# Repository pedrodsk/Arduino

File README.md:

# Arduino

## Some projects with arduino.

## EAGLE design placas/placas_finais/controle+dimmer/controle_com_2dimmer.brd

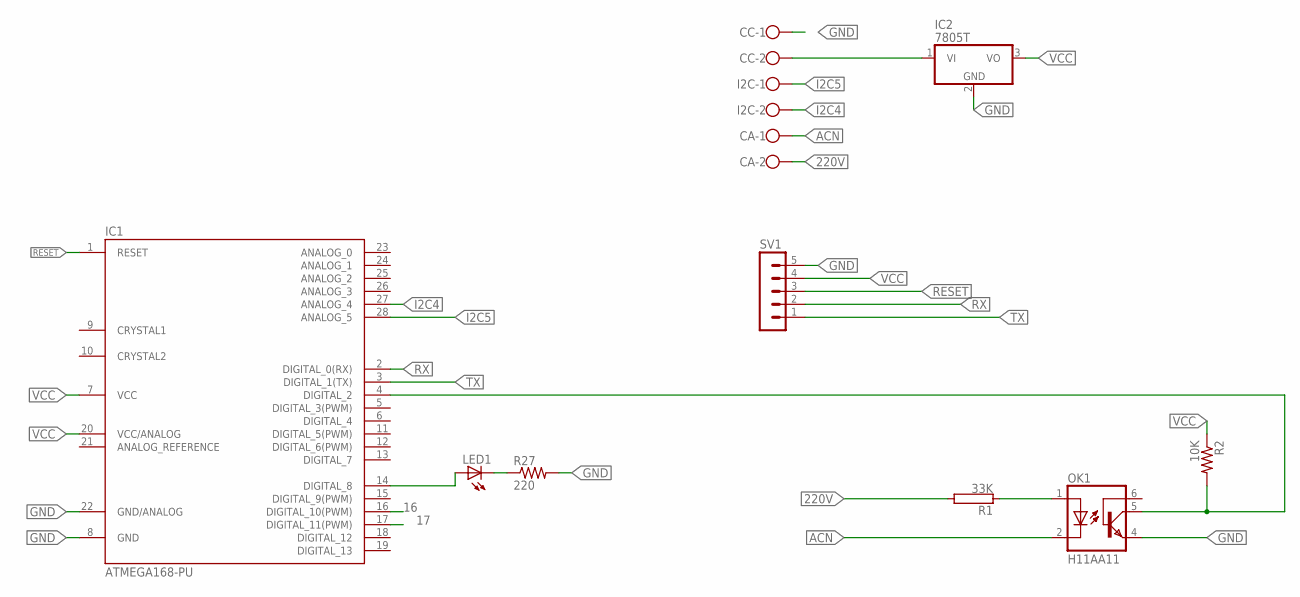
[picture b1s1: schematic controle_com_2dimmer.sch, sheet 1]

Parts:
CA: W237-102
CC: W237-102
I2C: W237-102
IC1: ATMEGA168-PU; DIL28-3
IC2: 7805T; TO220H
LED1: LED3MM
OK1: H11AA11; DIL06
R1: 33K; KH206-8R
R2: 10K; 0207/7
R27: 220; 0207/7
SV1: MA05-1

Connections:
16: IC1.16 (DIGITAL_10(PWM)); also elsewhere on the board
17: IC1.17 (DIGITAL_11(PWM)); also elsewhere on the board
220V: CA.2, R1.2; also elsewhere on the board
ACN: CA.1, OK1.2 (C)
DIG02: IC1.4 (DIGITAL_2), OK1.5 (COL), R2.2
GND: CC.1, IC1.8 (GND), IC1.22 (GND/ANALOG), IC2.2 (GND), OK1.4 (EMI), R27.2, SV1.5; also elsewhere on the board
I2C4: I2C.2, IC1.27 (ANALOG_4)
I2C5: I2C.1, IC1.28 (ANALOG_5)
unnamed: OK1.1 (A), R1.1
unnamed: LED1.K (C), R27.1
unnamed: CC.2, IC2.1 (VI)
unnamed: IC1.14 (DIGITAL_8), LED1.A
RESET: IC1.1 (RESET), SV1.3
RX: IC1.2 (DIGITAL_0(RX)), SV1.2
TX: IC1.3 (DIGITAL_1(TX)), SV1.1
VCC: IC1.7 (VCC), IC1.20 (VCC/ANALOG), IC2.3 (VO), R2.1, SV1.4

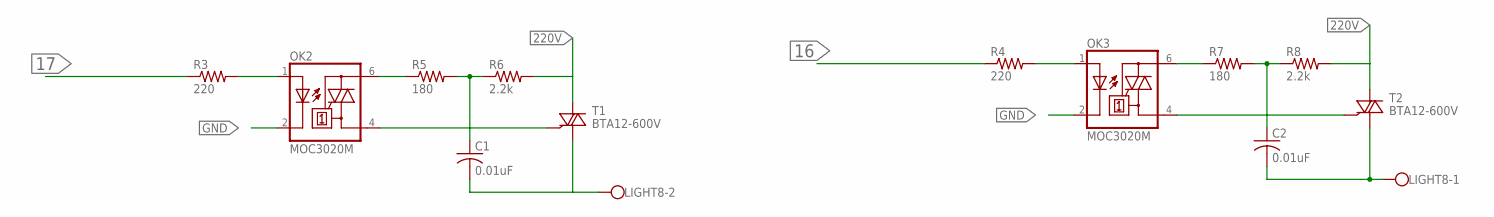
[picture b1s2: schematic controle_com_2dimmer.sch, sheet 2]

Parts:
C1, C2: 0.01uF; C075-042X103
LIGHT8: W237-102
OK2, OK3: MOC3020M; DIL06
R3, R4: 220; 0207/7
R5, R7: 180; 0309/10
R6, R8: 2.2k; 0309/10
T1, T2: BTA12-600V; TO220V

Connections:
16: R4.1; also elsewhere on the board
17: R3.1; also elsewhere on the board
220V: R6.2, R8.2, T1.2 (A2), T2.2 (A2); also elsewhere on the board
GND: OK2.2 (C), OK3.2 (C); also elsewhere on the board
unnamed: OK3.1 (A), R4.2
unnamed: OK2.1 (A), R3.2
unnamed: C1.1, R5.2, R6.1
unnamed: OK2.6 (A2), R5.1
unnamed: C1.2, LIGHT8.2, T1.1 (A1)
unnamed: OK2.4 (A1), T1.3 (G)
unnamed: C2.1, R7.2, R8.1
unnamed: OK3.6 (A2), R7.1
unnamed: C2.2, LIGHT8.1, T2.1 (A1)
unnamed: OK3.4 (A1), T2.3 (G)

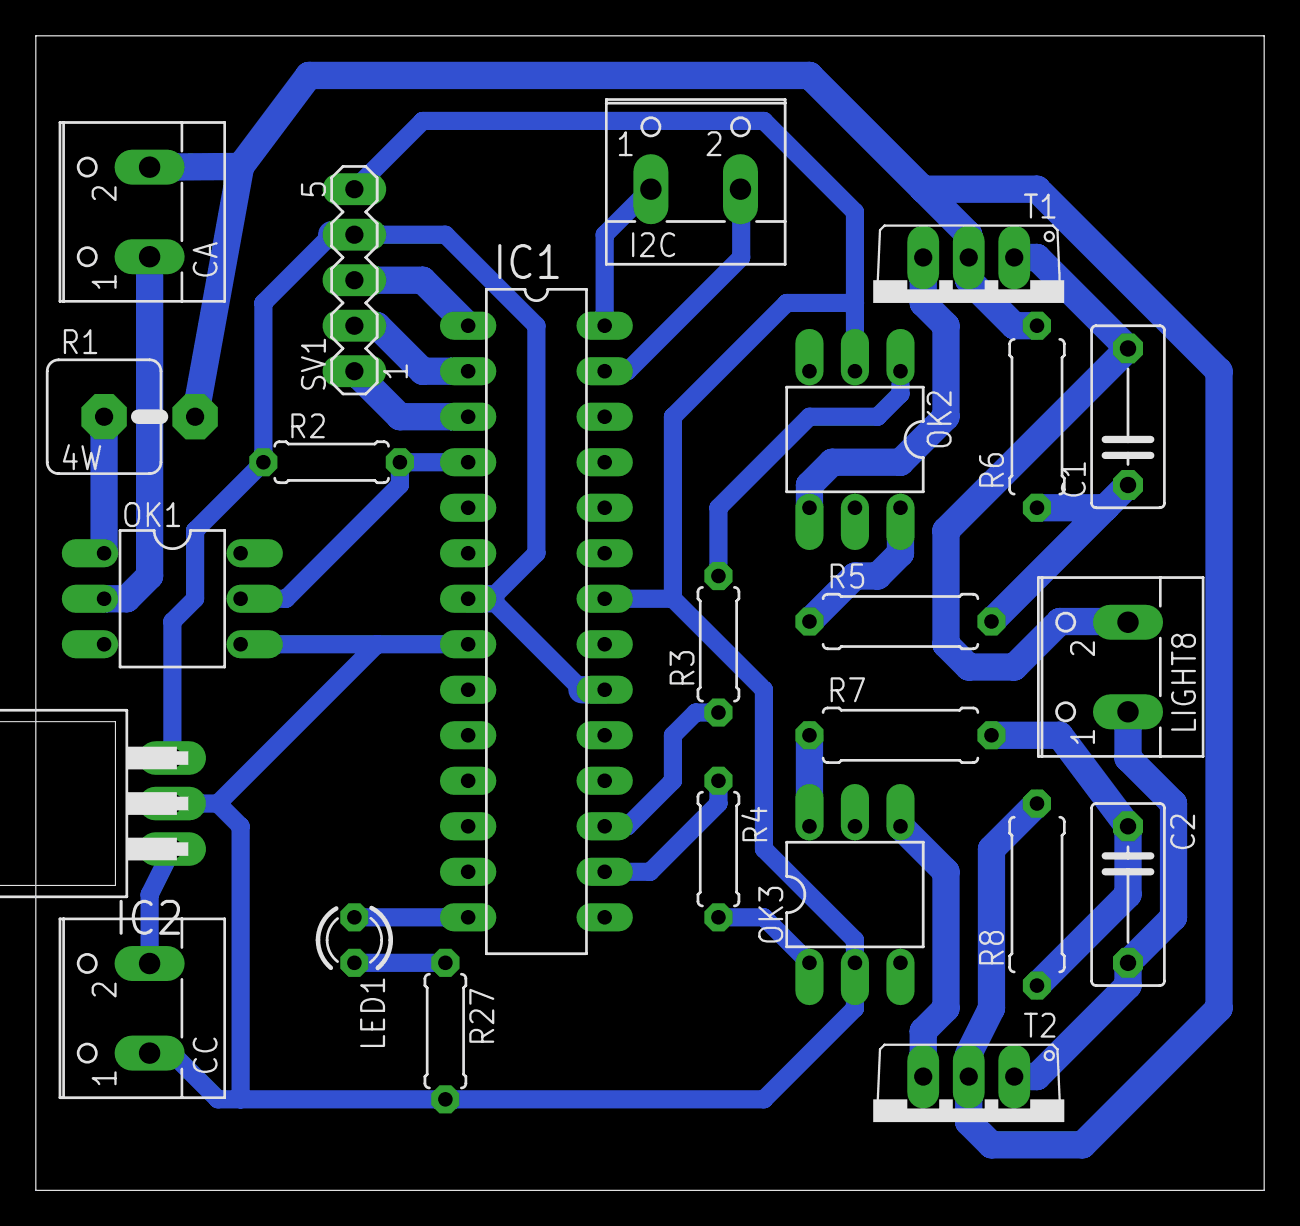
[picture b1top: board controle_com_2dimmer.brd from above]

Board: 2 copper layers, 68.6 x 64.4 mm, 24 parts (0 on the bottom side), 26 nets.

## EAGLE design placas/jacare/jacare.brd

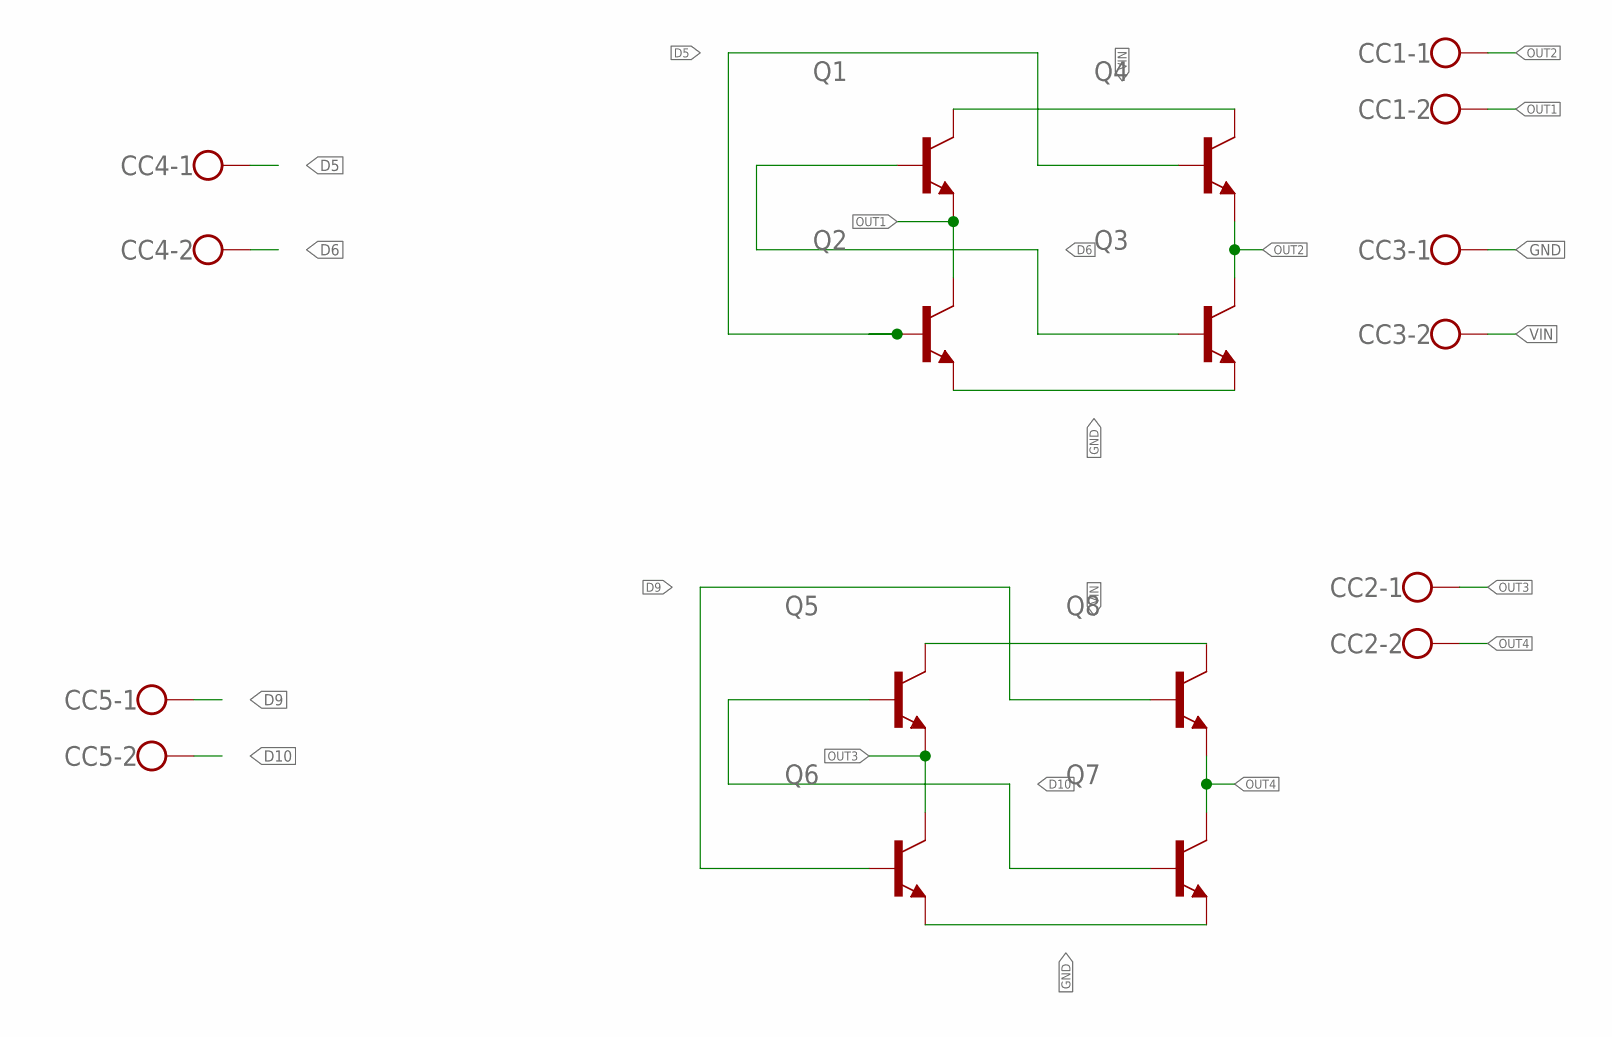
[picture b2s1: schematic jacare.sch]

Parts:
CC1, CC2, CC3, CC4, CC5: W237-102
Q1, Q2, Q3, Q4, Q5, Q6, Q7, Q8: -NPN-TO220V; TO220V

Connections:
D5: CC4.1, Q2.1 (B), Q4.1 (B)
D6: CC4.2, Q1.1 (B), Q3.1 (B)
D9: CC5.1, Q6.1 (B), Q8.1 (B)
D10: CC5.2, Q5.1 (B), Q7.1 (B)
GND: CC3.1, Q2.3 (E), Q3.3 (E), Q6.3 (E), Q7.3 (E)
OUT1: CC1.2, Q1.3 (E), Q2.2 (C)
OUT2: CC1.1, Q3.2 (C), Q4.3 (E)
OUT3: CC2.1, Q5.3 (E), Q6.2 (C)
OUT4: CC2.2, Q7.2 (C), Q8.3 (E)
VIN: CC3.2, Q1.2 (C), Q4.2 (C), Q5.2 (C), Q8.2 (C)

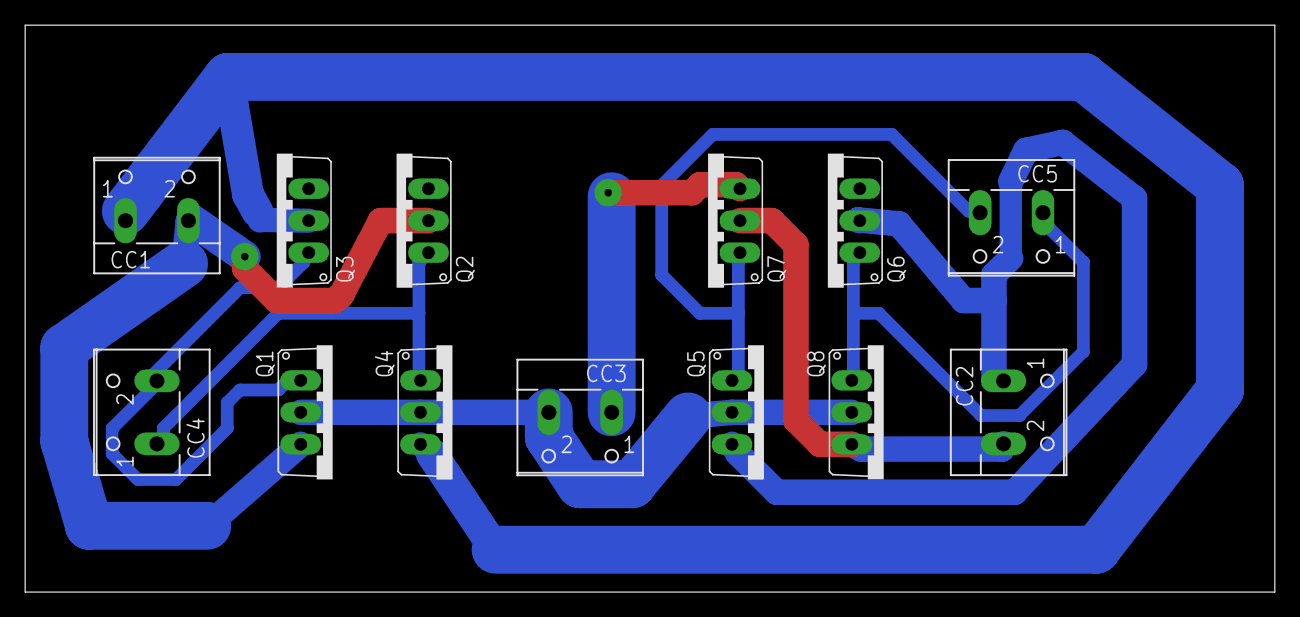
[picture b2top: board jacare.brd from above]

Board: 2 copper layers, 99.4 x 45.1 mm, 13 parts (0 on the bottom side), 10 nets.

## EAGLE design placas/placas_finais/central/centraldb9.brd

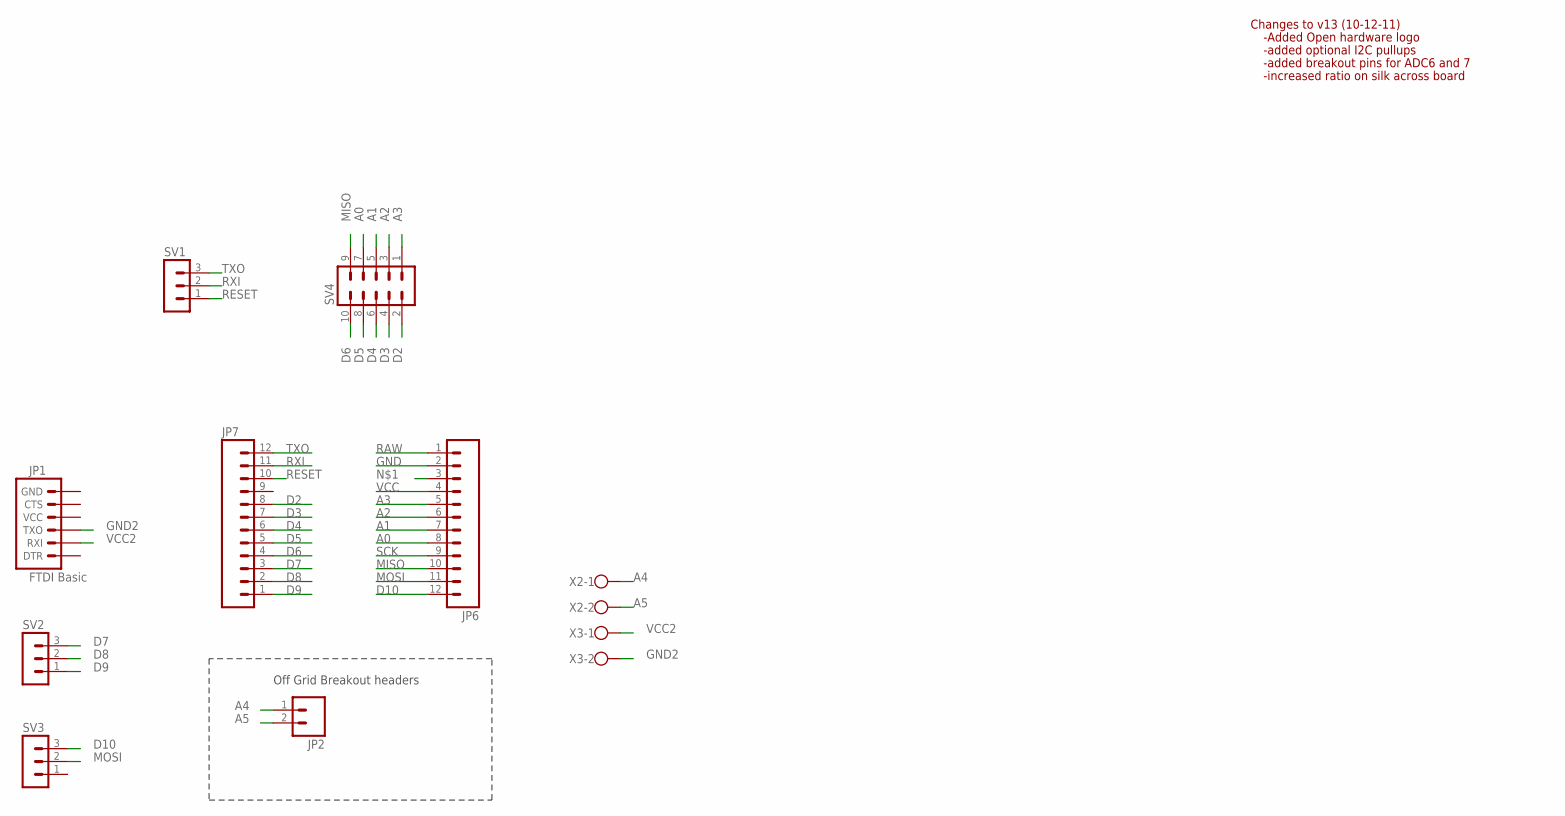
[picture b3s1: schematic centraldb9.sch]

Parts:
JP1: FTDI Basic; 1X06
JP2: M02PTH; 1X02
JP6, JP7: M12PTH; 1X12
SV1, SV2, SV3: MA03-1
SV4: MA05-2
X2, X3: W237-102

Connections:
A0: JP6.8, SV4.7
A1: JP6.7, SV4.5
A2: JP6.6, SV4.3
A3: JP6.5, SV4.1
A4: JP2.1, X2.1
A5: JP2.2, X2.2
D2: JP7.8, SV4.2
D3: JP7.7, SV4.4
D4: JP7.6, SV4.6
D5: JP7.5, SV4.8
D6: JP7.4, SV4.10
D7: JP7.3, SV2.3
D8: JP7.2, SV2.2
D9: JP7.1, SV2.1
D10: JP6.12, SV3.3
GND: JP6.2
GND2: JP1.3 (TXO), X3.2
MISO: JP6.10, SV4.9
MOSI: JP6.11, SV3.2
RAW: JP6.1
RESET: JP7.10, SV1.1
RXI: JP7.11, SV1.2
SCK: JP6.9
TXO: JP7.12, SV1.3
VCC: JP6.4
VCC2: JP1.2 (RXI), X3.1

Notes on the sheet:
Off Grid Breakout headers
Changes to v13 (10-12-11)
-Added Open hardware logo
-added optional I2C pullups
-added breakout pins for ADC6 and 7
-increased ratio on silk across board

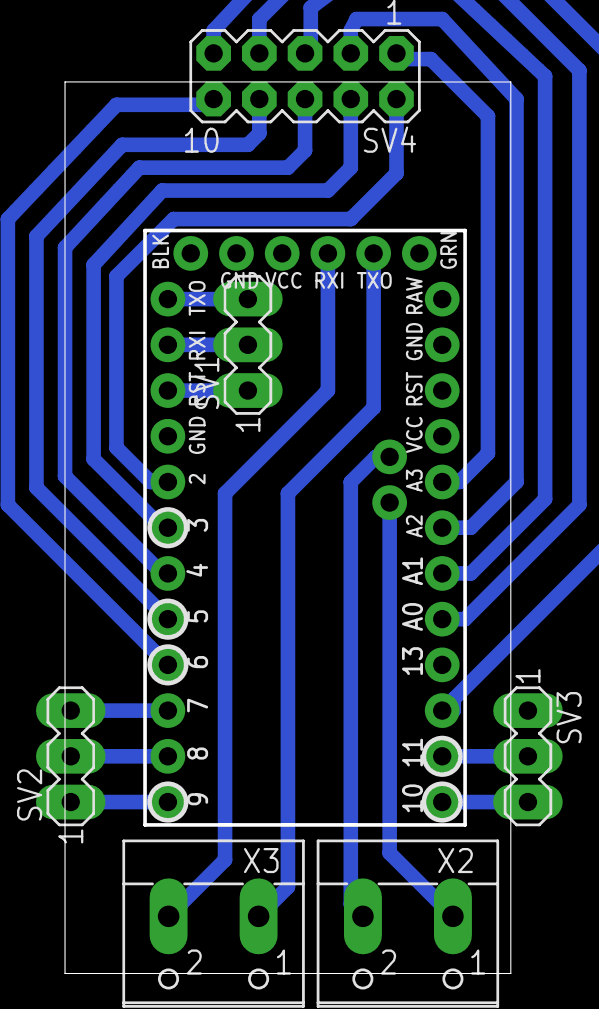
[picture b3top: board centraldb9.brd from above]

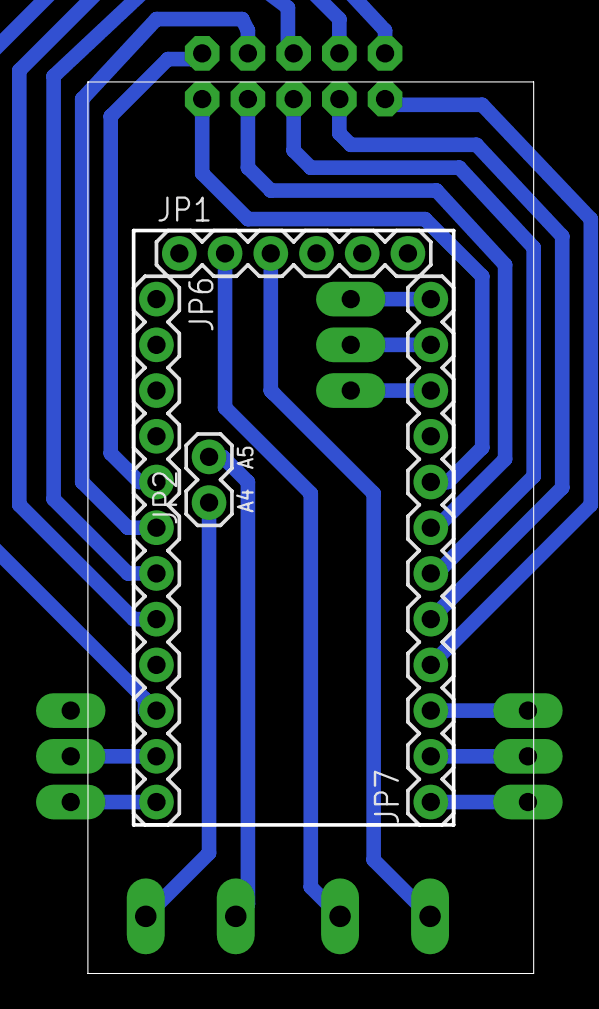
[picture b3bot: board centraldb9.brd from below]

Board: 2 copper layers, 24.8 x 49.5 mm, 10 parts (4 on the bottom side), 22 nets.

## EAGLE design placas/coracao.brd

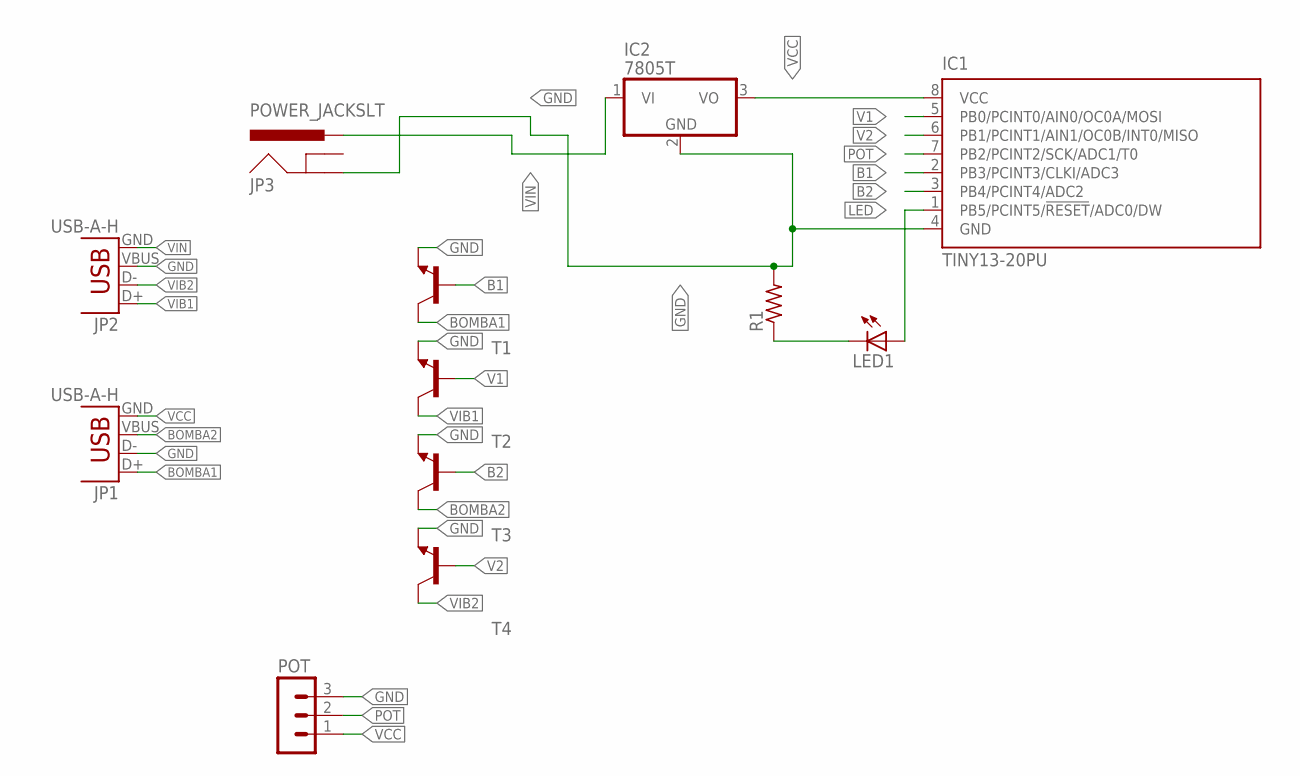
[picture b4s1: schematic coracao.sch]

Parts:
IC1: TINY13-20PU; DIL08
IC2: 7805T; TO220H
JP1, JP2: USB-A-H
JP3: POWER_JACKSLT; POWER_JACK_SLOT
LED1: LED5MM
POT: MA03-1
R1: R-US_0207/7; 0207/7
T1, T2, T3, T4: -NPN-TO220V; TO220V

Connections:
B1: IC1.2 (PB3/PCINT3/CLKI/ADC3), T1.1 (B)
B2: IC1.3 (PB4/PCINT4/ADC2), T3.1 (B)
BOMBA1: JP1.D+, T1.2 (C)
BOMBA2: JP1.VBUS, T3.2 (C)
GND: IC1.4 (GND), IC2.2 (GND), JP1.D-, JP2.VBUS, JP3.GND@2 (GND), POT.3, R1.2, T1.3 (E), T2.3 (E), T3.3 (E), T4.3 (E)
LED: IC1.1 (PB5/PCINT5/!RESET!/ADC0/DW), LED1.A
unnamed: LED1.K (C), R1.1
POT: IC1.7 (PB2/PCINT2/SCK/ADC1/T0), POT.2
V1: IC1.5 (PB0/PCINT0/AIN0/OC0A/MOSI), T2.1 (B)
V2: IC1.6 (PB1/PCINT1/AIN1/OC0B/INT0/MISO), T4.1 (B)
VCC: IC1.8 (VCC), IC2.3 (VO), JP1.GND, POT.1
VIB1: JP2.D+, T2.2 (C)
VIB2: JP2.D-, T4.2 (C)
VIN: IC2.1 (VI), JP2.GND, JP3.PWR

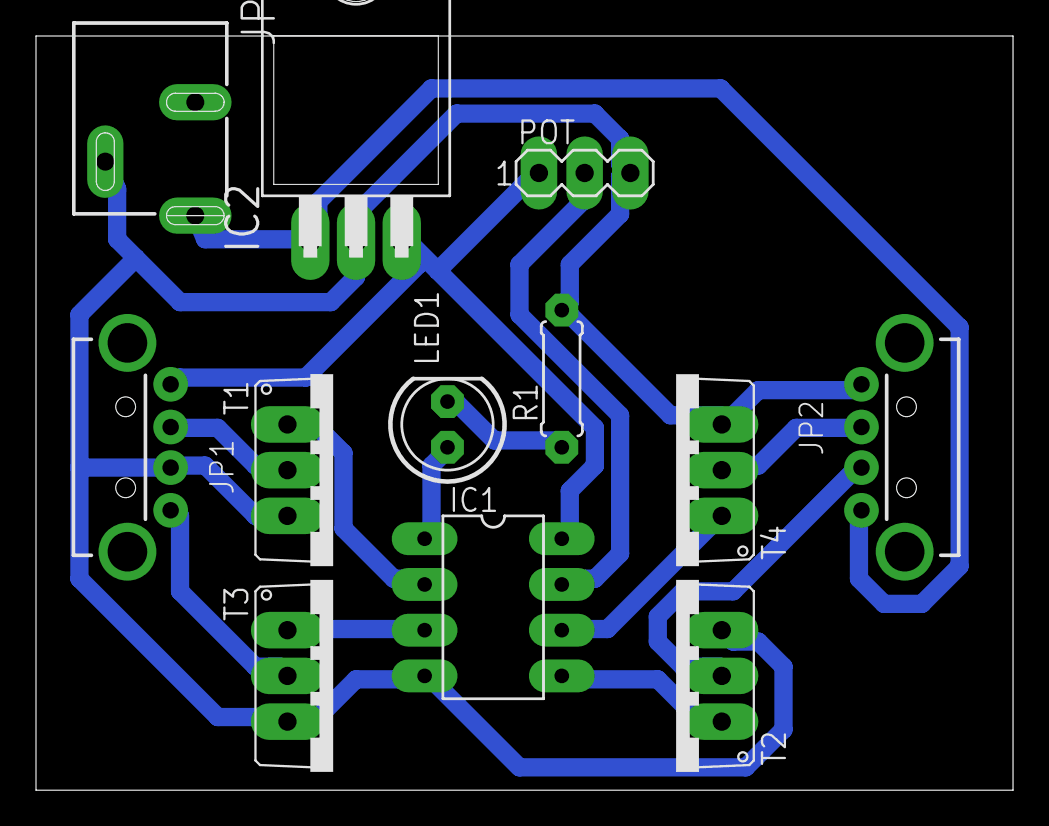
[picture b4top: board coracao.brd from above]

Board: 1 copper layer, 54.3 x 41.9 mm, 12 parts (0 on the bottom side), 14 nets.

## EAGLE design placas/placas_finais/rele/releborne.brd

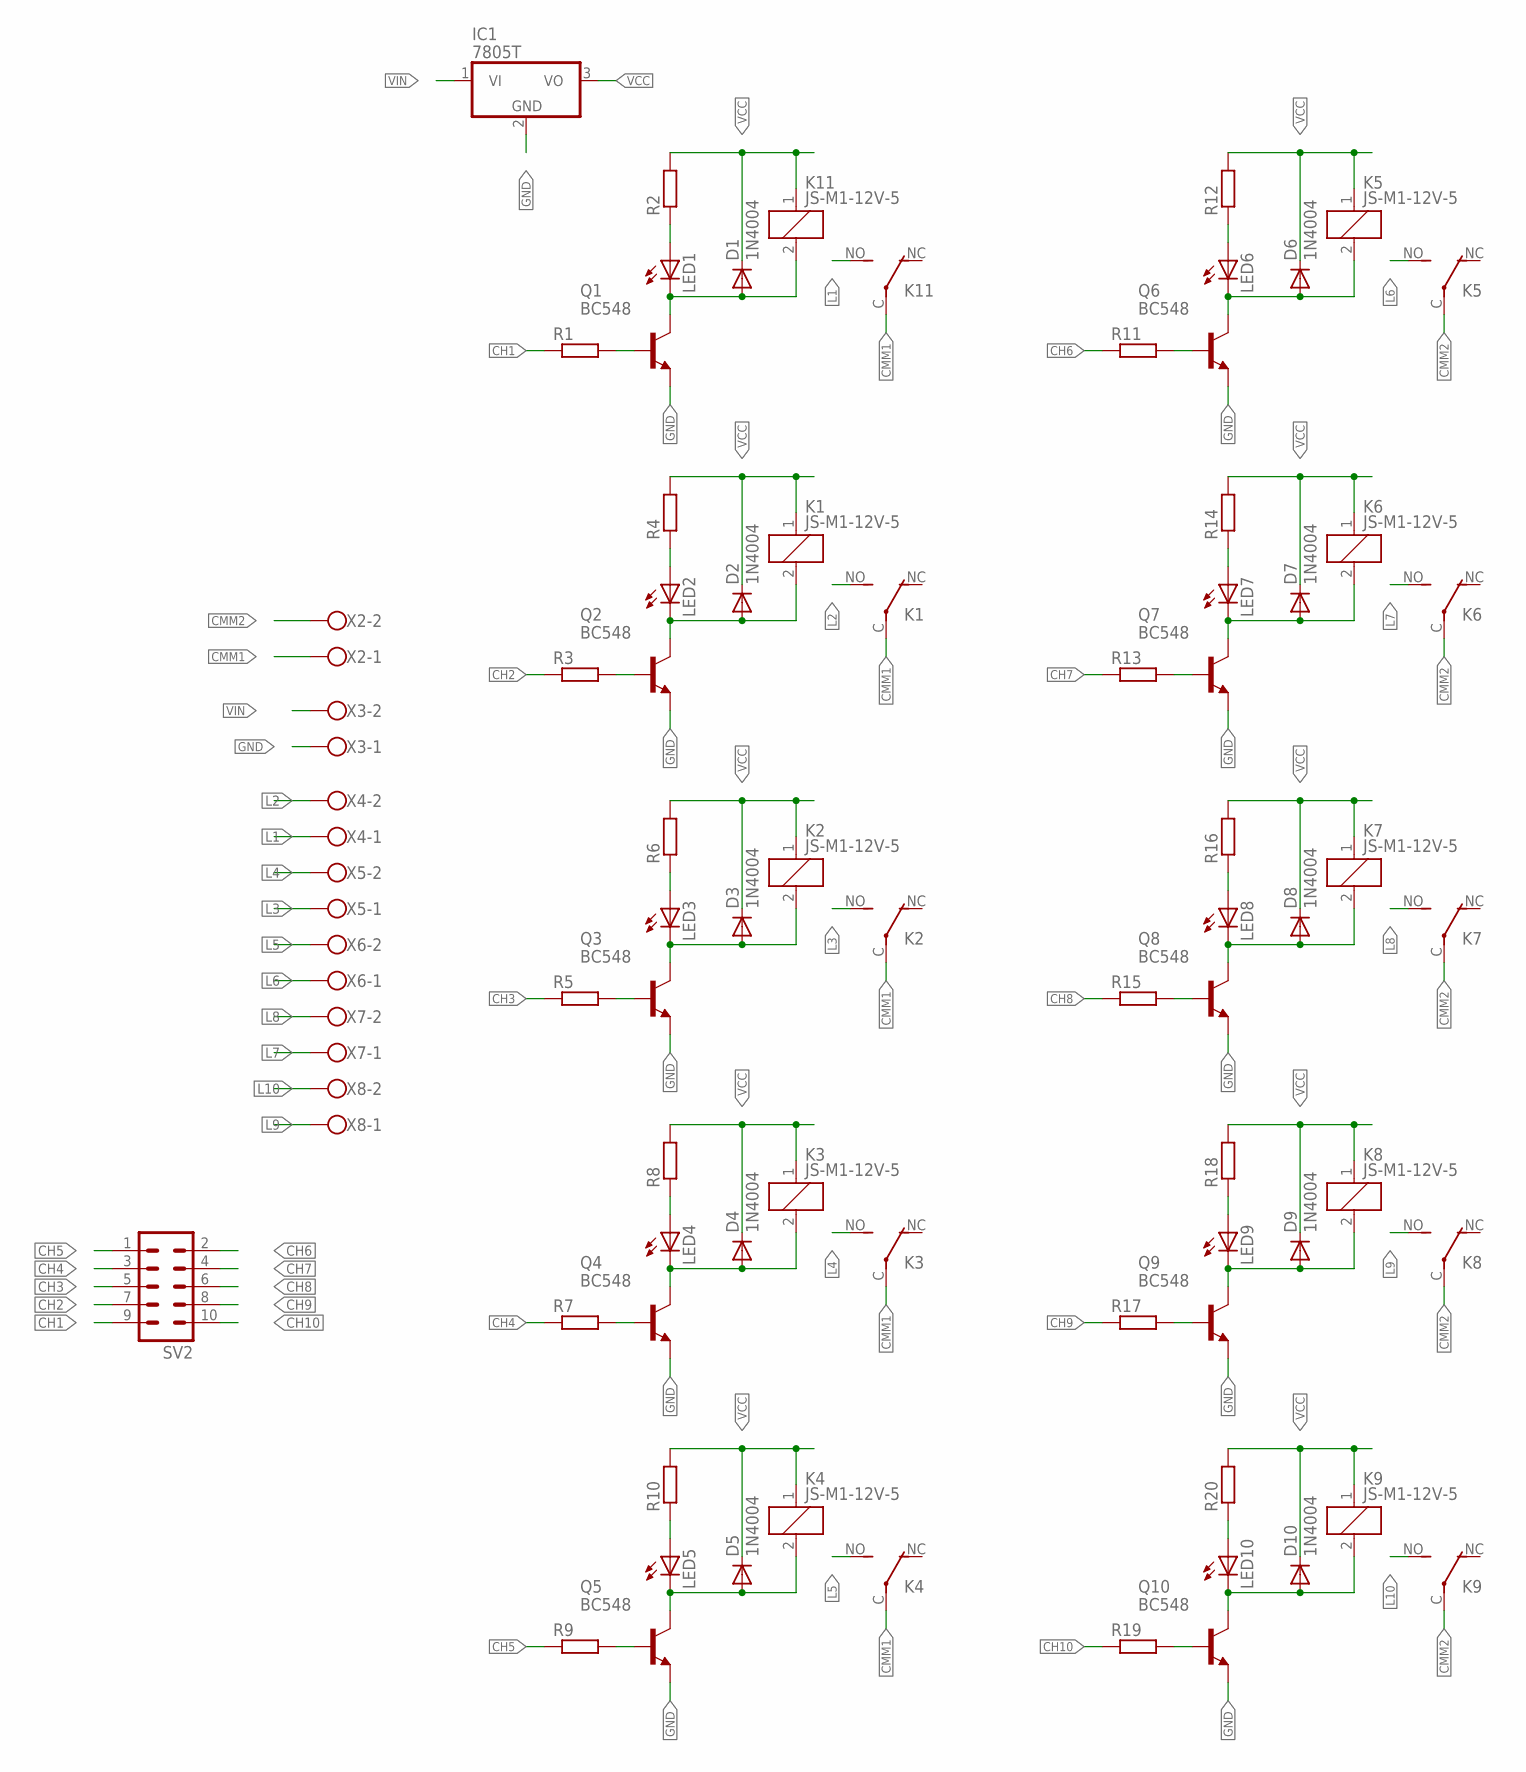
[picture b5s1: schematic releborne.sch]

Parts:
D1, D2, D3, D4, D5, D6, D7, D8, D9, D10: 1N4004; DO41-10
IC1: 7805T; TO220H
K1, K2, K3, K4, K5, K6, K7, K8, K9, K11: JS-M1-12V-5; JS-M
LED1, LED2, LED3, LED4, LED5, LED6, LED7, LED8, LED9, LED10: LED5MM
Q1, Q2, Q3, Q4, Q5, Q6, Q7, Q8, Q9, Q10: BC548; TO92-EBC
R1, R2, R3, R4, R5, R6, R7, R8, R9, R10, R11, R12, R13, R14, R15, R16, R17, R18, R19, R20: R-EU_0207/10; 0207/10
SV2: MA05-2
X2, X3, X4, X5, X6, X7, X8: W237-102

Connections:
CH1: R1.1, SV2.9
CH2: R3.1, SV2.7
CH3: R5.1, SV2.5
CH4: R7.1, SV2.3
CH5: R9.1, SV2.1
CH6: R11.1, SV2.2
CH7: R13.1, SV2.4
CH8: R15.1, SV2.6
CH9: R17.1, SV2.8
CH10: R19.1, SV2.10
CMM1: K1.C, K2.C, K3.C, K4.C, K11.C, X2.1
CMM2: K5.C, K6.C, K7.C, K8.C, K9.C, X2.2
GND: IC1.2 (GND), Q1.E, Q2.E, Q3.E, Q4.E, Q5.E, Q6.E, Q7.E, Q8.E, Q9.E, Q10.E, X3.1
L1: K11.NO (S), X4.1
L2: K1.NO (S), X4.2
L3: K2.NO (S), X5.1
L4: K3.NO (S), X5.2
L5: K4.NO (S), X6.2
L6: K5.NO (S), X6.1
L7: K6.NO (S), X7.1
L8: K7.NO (S), X7.2
L9: K8.NO (S), X8.1
L10: K9.NO (S), X8.2
unnamed: Q1.B, R1.2
unnamed: LED1.A, R2.1
unnamed: Q2.B, R3.2
unnamed: LED2.A, R4.1
unnamed: D1.A, K11.2, LED1.K (C), Q1.C
unnamed: D2.A, K1.2, LED2.K (C), Q2.C
unnamed: Q3.B, R5.2
unnamed: LED3.A, R6.1
unnamed: D3.A, K2.2, LED3.K (C), Q3.C
unnamed: Q4.B, R7.2
unnamed: LED4.A, R8.1
unnamed: D4.A, K3.2, LED4.K (C), Q4.C
unnamed: Q5.B, R9.2
unnamed: LED5.A, R10.1
unnamed: D5.A, K4.2, LED5.K (C), Q5.C
unnamed: Q6.B, R11.2
unnamed: LED6.A, R12.1
unnamed: D6.A, K5.2, LED6.K (C), Q6.C
unnamed: Q7.B, R13.2
unnamed: LED7.A, R14.1
unnamed: D7.A, K6.2, LED7.K (C), Q7.C
unnamed: Q8.B, R15.2
unnamed: LED8.A, R16.1
unnamed: D8.A, K7.2, LED8.K (C), Q8.C
unnamed: Q9.B, R17.2
unnamed: LED9.A, R18.1
unnamed: D9.A, K8.2, LED9.K (C), Q9.C
unnamed: Q10.B, R19.2
unnamed: LED10.A, R20.1
unnamed: D10.A, K9.2, LED10.K (C), Q10.C
VCC: D1.C, D2.C, D3.C, D4.C, D5.C, D6.C, D7.C, D8.C, D9.C, D10.C, IC1.3 (VO), K1.1, K2.1, K3.1, K4.1, K5.1, K6.1, K7.1, K8.1, K9.1, K11.1, R2.2, R4.2, R6.2, R8.2, R10.2, R12.2, R14.2, R16.2, R18.2, R20.2
VIN: IC1.1 (VI), X3.2

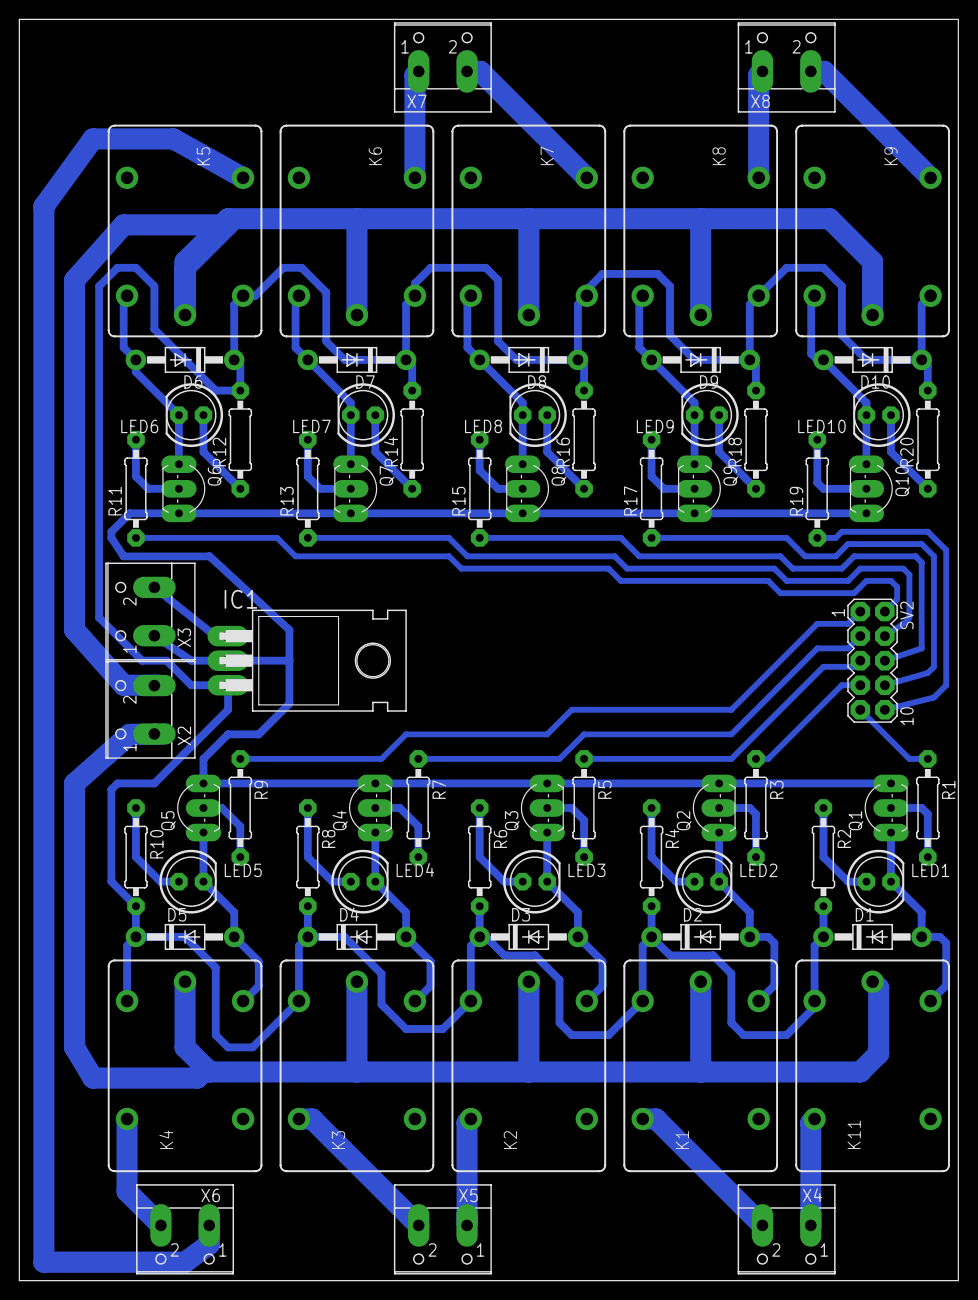
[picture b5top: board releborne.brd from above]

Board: 2 copper layers, 97.1 x 130.5 mm, 69 parts (0 on the bottom side), 55 nets.

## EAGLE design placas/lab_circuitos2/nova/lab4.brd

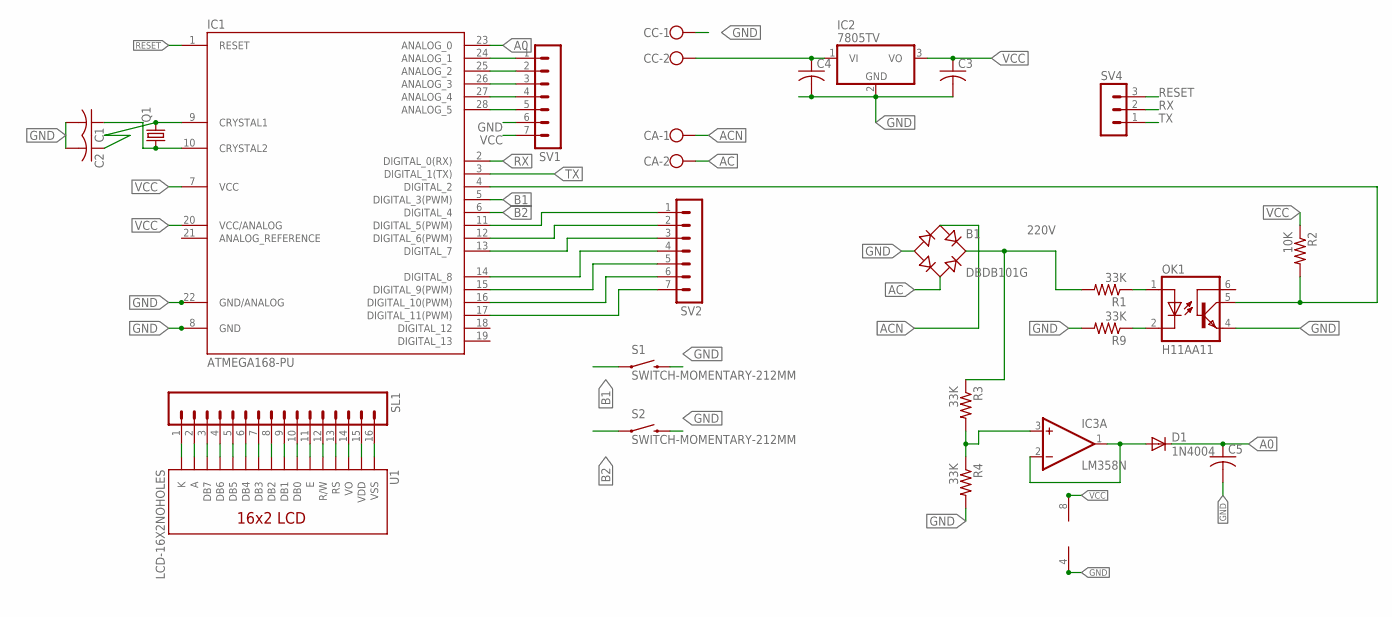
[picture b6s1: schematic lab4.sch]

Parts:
B1: DBDB101G; DB
C1, C2: C-US025-025X050; C025-025X050
C3: C-US075-032X103; C075-032X103
C4: C-US050-025X075; C050-025X075
C5: C-US050-075X075; C050-075X075
CA: W237-102
CC: W237-102
D1: 1N4004; DO41-10
IC1: ATMEGA168-PU; DIL28-3
IC2: 7805TV; TO220V
IC3: LM358N; DIL08
OK1: H11AA11; DIL06
Q1: CRYSTALHC18U-V; HC18U-V
R1, R3, R4, R9: 33K; 0207/7
R2: 10K; 0309/12
S1, S2: SWITCH-MOMENTARY-212MM; TACTILE-PTH-12MM
SL1: MA16; 16PA
SV1, SV2: MA07-1
SV4: MA03-1
U1: LCD-16X2NOHOLES; LCD-16X2_NOHOLES

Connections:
220V: B1.+, R1.2, R3.1
A0: C5.1, D1.C, IC1.23 (ANALOG_0)
AC: B1.AC2, CA.2
ACN: B1.AC1, CA.1
B1: IC1.5 (DIGITAL_3(PWM)), S1.1
B2: IC1.6 (DIGITAL_4), S2.1
DIG02: IC1.4 (DIGITAL_2), OK1.5 (COL), R2.2
GND: B1.-, C1.2, C2.2, C3.2, C4.2, C5.2, CC.1, IC1.8 (GND), IC1.22 (GND/ANALOG), IC2.2 (GND), IC3.4 (V-), OK1.4 (EMI), R4.2, R9.2, S1.3 (2), S2.3 (2), SV1.6
unnamed: IC1.24 (ANALOG_1), SV1.1
unnamed: D1.A, IC3.1 (OUT), IC3.2 (-IN)
unnamed: IC3.3 (+IN), R3.2, R4.1
unnamed: OK1.2 (C), R9.1
unnamed: IC1.11 (DIGITAL_5(PWM)), SV2.1
unnamed: OK1.1 (A), R1.1
unnamed: IC1.25 (ANALOG_2), SV1.2
unnamed: C2.1, IC1.9 (CRYSTAL1), Q1.2
unnamed: C1.1, IC1.10 (CRYSTAL2), Q1.1
unnamed: IC1.12 (DIGITAL_6(PWM)), SV2.2
unnamed: IC1.13 (DIGITAL_7), SV2.3
unnamed: C4.1, CC.2, IC2.1 (VI)
unnamed: IC1.14 (DIGITAL_8), SV2.4
unnamed: IC1.15 (DIGITAL_9(PWM)), SV2.5
unnamed: IC1.16 (DIGITAL_10(PWM)), SV2.6
unnamed: IC1.26 (ANALOG_3), SV1.3
unnamed: IC1.17 (DIGITAL_11(PWM)), SV2.7
unnamed: IC1.27 (ANALOG_4), SV1.4
unnamed: IC1.28 (ANALOG_5), SV1.5
unnamed: SL1.1, U1.16 (K)
unnamed: SL1.2, U1.15 (A)
unnamed: SL1.3, U1.14 (DB7)
unnamed: SL1.4, U1.13 (DB6)
unnamed: SL1.5, U1.12 (DB5)
unnamed: SL1.6, U1.11 (DB4)
unnamed: SL1.7, U1.10 (DB3)
unnamed: SL1.8, U1.9 (DB2)
unnamed: SL1.9, U1.8 (DB1)
unnamed: SL1.10, U1.7 (DB0)
unnamed: SL1.11, U1.6 (E)
unnamed: SL1.12, U1.5 (R/W)
unnamed: SL1.13, U1.4 (RS)
unnamed: SL1.14, U1.3 (VO)
unnamed: SL1.15, U1.2 (VDD)
unnamed: SL1.16, U1.1 (VSS)
RESET: IC1.1 (RESET), SV4.3
RX: IC1.2 (DIGITAL_0(RX)), SV4.2
TX: IC1.3 (DIGITAL_1(TX)), SV4.1
VCC: C3.1, IC1.7 (VCC), IC1.20 (VCC/ANALOG), IC2.3 (VO), IC3.8 (V+), R2.1, SV1.7

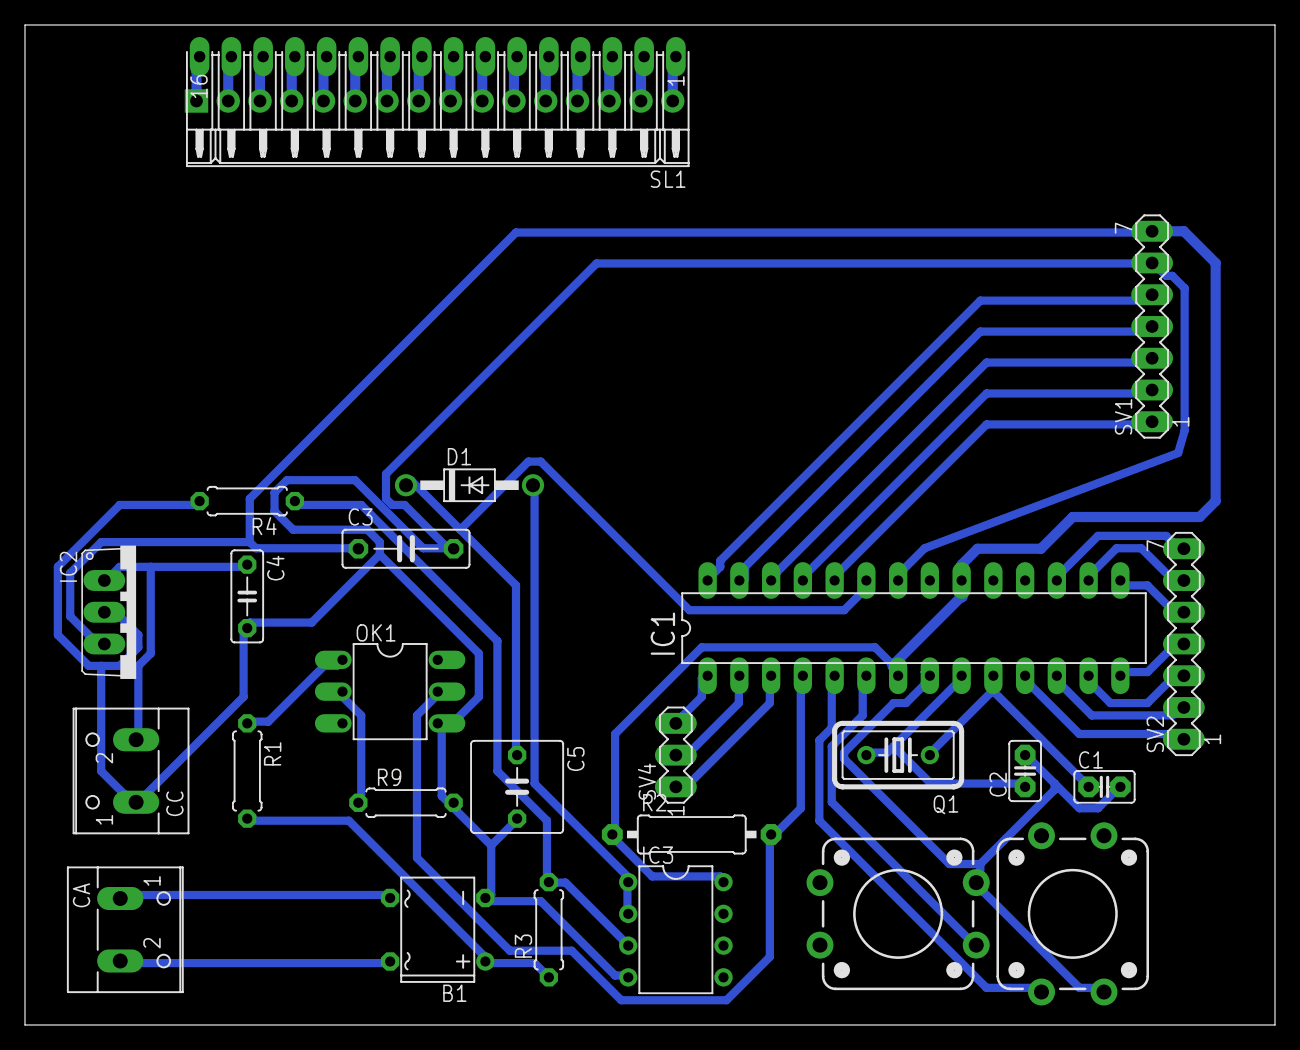
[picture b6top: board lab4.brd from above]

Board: 2 copper layers, 100.0 x 80.0 mm, 26 parts (0 on the bottom side), 47 nets.

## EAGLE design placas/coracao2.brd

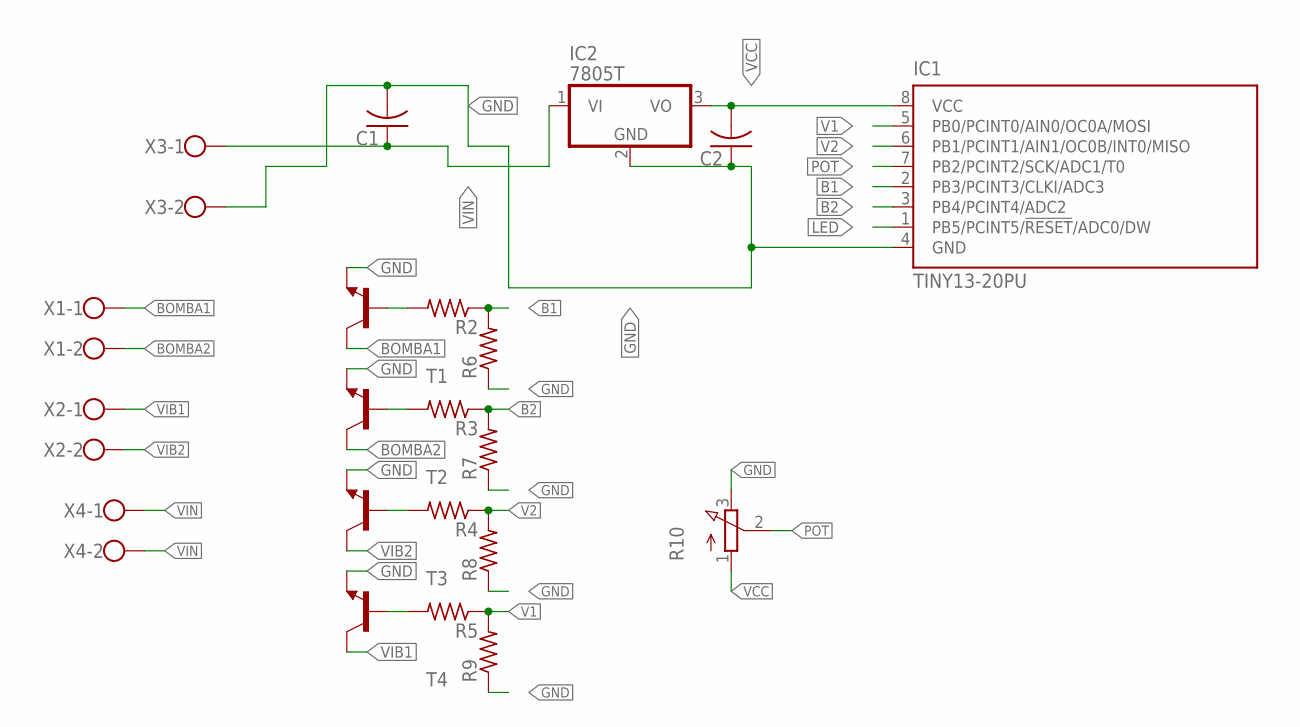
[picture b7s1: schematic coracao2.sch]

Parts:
C1, C2: C-US025-025X050; C025-025X050
IC1: TINY13-20PU; DIL08
IC2: 7805T; TO220H
R2, R3, R4, R5, R6, R7, R8, R9: R-US_0207/9; 0207/9
R10: 3RP/1610N
T1, T2, T3, T4: -NPN-TO220V; TO220V
X1, X2, X3, X4: W237-102

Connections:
B1: IC1.2 (PB3/PCINT3/CLKI/ADC3), R2.1, R6.2
B2: IC1.3 (PB4/PCINT4/ADC2), R3.1, R4.2, R7.2, T3.1 (B)
BOMBA1: T1.2 (C), X1.1
BOMBA2: T2.2 (C), X1.2
GND: C1.2, C2.1, IC1.4 (GND), IC2.2 (GND), R6.1, R7.1, R8.1, R9.1, R10.3 (E), T1.3 (E), T2.3 (E), T3.3 (E), T4.3 (E), X3.2
LED: IC1.1 (PB5/PCINT5/!RESET!/ADC0/DW)
unnamed: R2.2, T1.1 (B)
unnamed: R3.2, T2.1 (B)
unnamed: R5.2, T4.1 (B)
POT: IC1.7 (PB2/PCINT2/SCK/ADC1/T0), R10.2 (S)
V1: IC1.5 (PB0/PCINT0/AIN0/OC0A/MOSI), R5.1, R9.2
V2: IC1.6 (PB1/PCINT1/AIN1/OC0B/INT0/MISO), R4.1, R8.2
VCC: C2.2, IC1.8 (VCC), IC2.3 (VO), R10.1 (A)
VIB1: T4.2 (C), X2.1
VIB2: T3.2 (C), X2.2
VIN: C1.1, IC2.1 (VI), X3.1, X4.1, X4.2

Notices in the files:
parts and their libraries:
SparkFun-Connectors: Licensing: Creative Commons ShareAlike 4.0 International - https://creativecommons.org/licenses/by-sa/4.0
